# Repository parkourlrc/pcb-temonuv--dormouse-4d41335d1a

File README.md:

<div align="center">

# 🐭 Dormouse

**A tiny, coin-cell Zigbee climate sensor that hibernates like its namesake — years on a CR2032, and joins Home Assistant with zero cloud.**

[-2f6db3)](https://www.silabs.com/wireless/zigbee)

</div>

---

## What it is

**Dormouse** is a from-scratch, open-hardware **temperature + humidity sensor** on the
Silicon Labs **MGM210LA22JNF2** module (EFR32MG21, Cortex-M33, 2.4 GHz). It's a Zigbee
**sleepy end device**: it wakes every 5 minutes, reads an external **Sensirion SHT40**
over I²C, reports temperature, relative humidity and battery level over Zigbee, then
drops back to EM2 sleep. On a single **CR2032** that budgets out to **multi-year**
battery life. No hub beyond your existing Zigbee coordinator, no cloud, no vendor lock-in.

> **Why "Dormouse"?** A dormouse hibernates and briefly stirs to feed — which is
> exactly what a Zigbee sleepy end device does: sleep deep in EM2, wake for a few
> milliseconds every five minutes, report, and doze off again.

Everything is here: **firmware**, a **custom KiCad schematic + routed 2-layer PCB**,
a **datasheet-exact module footprint**, the **manufacturing files**, and the
**Home Assistant integration**.

## ✨ Highlights

- 🔋 **Coin-cell native** — sleepy end device, EM2 sleep, TX power capped so a CR2032 never browns out. ~1–3 µA average.
- 🌡️ **Real ambient temp + humidity** — external SHT40 (±0.2 °C / ±1.8 %RH), CRC-checked, one-shot read per wake.
- 🏠 **Zero-config Home Assistant** — temperature, humidity and battery auto-expose over **ZHA**; a ready-made **Zigbee2MQTT** converter is included.
- 🐞 **Runtime debug mode** — flip a switch in HA to drop to 10 s sampling and stream a live log line, over a manufacturer-specific Zigbee cluster. Auto-off on boot so it never drains the cell.
- 🛡️ **Self-healing** — software watchdog (spans the multi-minute sleep), I²C bus recovery, and a **button-less factory reset** (power-cycle 5× quickly → re-commission).
- 🛠️ **Fully open & reproducible** — headless `slc generate` → build → flash; schematic + footprint generated by scripts; DRC-clean routed board; Gerbers included.

---

## 📸 Gallery

| Top | Bottom (CR2032 holder) |
|:---:|:---:|
|  |  |

<div align="center"></div>

---

## 🧩 How it works

```
         ┌──────────────────────────── every 5 min (10 s in debug) ────────────────────────────┐
         │                                                                                      │
   wake ─┤  SHT40 read (I²C, CRC)  →  IADC battery read  →  write ZCL attrs  →  reporting  →  EM2 sleep
         │        temp + RH               VDD via AVDD/4        temp/RH/batt      pushes to
         │                                                                        coordinator
         └──────────────────────────────────────────────────────────────────────────────────────┘

  ZCL model (endpoint 1, HA Temperature Sensor 0x0302):
    Basic · Power Config · Identify · Temperature (0x0402) · Humidity (0x0405) · MGM Debug (0xFC10)
```

The `.slcp` manifest is the **source of truth** for components, the target part,
sleepy-device timing and TX power. The ZCL data model lives in a ZAP file; the
`#define`s in `src/app.h` mirror it. See [`CLAUDE.md`](CLAUDE.md) for the full
architecture write-up.

---

## 🔧 Hardware

Tiny **2-layer, ~36 × 25 mm** board. The MGM210L sits at the top edge with its
**integrated antenna** pointing off-board and a copper keepout around it; the
CR2032 holder is on the back; the SHT40 is at the bottom edge for airflow.

### Bill of materials

| Ref | Part | Purpose |
|-----|------|---------|
| U1 | **MGM210LA22JNF2** | MCU + Zigbee radio (integrated antenna) |
| U2 | **Sensirion SHT40** (SHT40-AD1B) | Temp + humidity, I²C 0x44 |
| BT1 | CR2032 SMD holder | Power (~220 mAh) |
| R1, R2 | 4.7 kΩ (0402) | I²C pull-ups |
| C1 | 10 µF (0805) | Bulk decoupling — sources the TX pulse |
| C2, C3 | 100 nF (0402) | HF decoupling (module + sensor) |
| J1 | 1×5 1.27 mm header | SWD / RTT debug |

Full wiring, pinout and CR2032 power design: **[`docs/hardware.md`](docs/hardware.md)**.
KiCad sources, custom libraries and PCB notes: **[`hardware/README.md`](hardware/README.md)**.
Manufacturing files (Gerbers, drill, BOM, pick-and-place): **[`hardware/fab/`](hardware/fab/)**.

---

## 🚀 Build & flash

There is **no host/unit-test suite** — this is on-target firmware. "Testing" means
flashing and watching the join + reports over RTT and in ZHA/Z2M. The toolchain is
installed via **SLT** (Silicon Labs Tool).

```bash
# one-time: install SDK 2026.6.0 + slc/gcc/zap/commander
slt install -f tools/pkg.slt

source tools/env.sh      # puts slc, arm-none-eabi-gcc, commander, zap on PATH
tools/build.sh           # slc generate (runs ZAP) + make  ->  build/…/*.s37
tools/flash.sh           # commander flash over J-Link
commander rtt --device MGM210LA22JNF   # live device logs
```

Then put your Zigbee network in join mode (ZHA: *Add device*; Z2M: `permit_join`)
and power the sensor. Verified working with SDK 2026.6.0, slc-cli 6.0.22, GCC 14.2.

---

## 🏠 Home Assistant

- **ZHA** — temperature, humidity and battery are **zero-config** (standard clusters).
  The custom debug cluster needs a small [ZHA quirk](https://github.com/zigpy/zha-device-handlers) to expose.
- **Zigbee2MQTT** — drop [`integration/zigbee2mqtt/dormouse.js`](integration/zigbee2mqtt/dormouse.js)
  in as an external converter. It exposes temperature, humidity, battery, and the
  debug entities (`debug_mode` switch, `debug_log`, `debug_status`, `sample_interval`).

---

## 🗂️ Repository layout

| Path | What |
|------|------|
| `mgm210l_zigbee_temp.slcp` | Project manifest — components, target, config. **Source of truth.** |
| `src/` | Firmware: measurement loop, SHT40 driver, battery, debug mode, watchdog, factory reset. |
| `config/zcl/` | ZCL data model (ZAP) + custom debug-cluster XML. |
| `hardware/` | KiCad schematic + routed PCB, custom symbol/footprint libraries, generators. |
| `hardware/fab/` | Gerbers, drill, BOM, pick-and-place — ready to send to a fab. |
| `integration/zigbee2mqtt/` | Z2M external converter. |
| `docs/` | Hardware guide + rendered images. |
| `tools/` | Headless build / flash / env scripts. |
| `CLAUDE.md` | Deep-dive architecture & rationale (great first read for contributors). |

---

## 🗺️ Roadmap

### ✅ Done
- [x] Firmware builds end-to-end (`slc generate` → compile → link → flashable `.s37`)
- [x] ZCL model: temperature, humidity, power config, + manufacturer debug cluster (`0xFC10`)
- [x] SHT40 I²C driver — CRC-8 verified, with automatic I²C bus recovery + one retry
- [x] Battery sensing via internal IADC (no divider), with a bounded busy-wait guard
- [x] Sleepy-end-device power model (EM2 sleep, 300 s poll, 8 dBm TX cap)
- [x] Runtime debug mode (HA-controlled 10 s cadence + live log), auto-off on boot
- [x] Software watchdog (sleeptimer-based, spans multi-minute sleep)
- [x] Button-less power-cycle factory reset (5× quick cycles → re-commission)
- [x] Custom, datasheet-exact MGM210LA22JNF land pattern + symbol library
- [x] 2-layer PCB fully routed, GND pours with antenna keepout, **0 copper DRC errors**
- [x] Manufacturing package generated (Gerbers / drill / BOM / pick-and-place)
- [x] **PCBs ordered** 🎉
- [x] Zigbee2MQTT converter + ZHA zero-config path
- [x] GitHub Actions CI — repo + device-identity checks on every push (`ci.yml`); firmware `.s37` build & release via a self-hosted runner (`firmware.yml`)

### 🔜 Next (hardware bring-up)
- [ ] Assemble the boards (reflow / hand-solder), first power-on
- [ ] Flash and confirm join + temperature/humidity/battery reports in ZHA & Z2M
- [ ] Verify TX power reads 8 dBm on RTT after a warm-reboot join
- [ ] Confirm `FACTORY_RESET_NVM3_KEY` has no stack-key collision; test the 5× power-cycle reset
- [ ] Double-check `config/sl_i2cspm_sensor_config.h` pins match the built board (PC00/PC01)
- [ ] Measure real sleep current & validate multi-year battery estimate

### 💡 Ideas / help wanted
- [ ] ZHA quirk (zha-device-handlers) so the debug cluster shows up as HA entities
- [ ] 3D model for the custom MGM210L footprint (nicer renders + mechanical check)
- [ ] 3D-printed enclosure / vented case for the SHT40
- [ ] Production build profile (drop `segger_rtt` / `iostream_rtt` to shave idle current)
- [ ] Si7021 sensor variant (swap command byte + conversion only)
- [ ] Zigbee OTA firmware update support
- [ ] Nudge the one SDA trace to clear the cosmetic 0.05 mm edge-clearance DRC note

---

## 🤝 Contributing

Issues and PRs welcome — especially hardware bring-up reports, battery-life data,
and the "help wanted" items above. Please read [`CLAUDE.md`](CLAUDE.md) first; it
explains the two-stage build, the `.slcp`-is-truth rule, and the ZCL/`app.h`/converter
sync requirement that's easy to trip over.

## 📄 License

MIT — see [`LICENSE`](LICENSE). Firmware builds against the Silicon Labs Simplicity
SDK, which carries its own (permissive) license; it is **not** vendored here — the
build fetches it via SLT.

## 🙏 Acknowledgements

- Silicon Labs — EFR32MG21 / MGM210L, Simplicity SDK, Zigbee stack.
- Sensirion — SHT4x sensor family.
- The **KiCad**, **Freerouting**, and **Zigbee2MQTT** projects.

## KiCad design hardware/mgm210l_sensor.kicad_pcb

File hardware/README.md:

# Hardware — schematic + PCB

KiCad 8/9 design for **Dormouse**, the MGM210L CR2032 temperature + humidity
sensor. The schematic (electrical connectivity) and the routed PCB are both here.
(File basenames stay `mgm210l_sensor.*` — renaming a finalized, already-ordered
KiCad project risks breaking internal references for no functional gain.)

| File | What |
|------|------|
| `mgm210l_sensor.kicad_pro` | KiCad project — open this in KiCad. |
| `mgm210l_sensor.kicad_sch` | Schematic (generated by `gen_sch.py`). |
| `mgm210l_sensor.kicad_pcb` | PCB — placement + antenna keepout + GND pours + full routing. |
| `mgm210l_sensor.pdf` | Rendered schematic (quick view, no KiCad needed). |
| `mgm210l_sensor_2d_view.png` | Rendered PCB (top view). |
| `mgm210l_sensor_enclosure_drawing.pdf` | Dimensioned mechanical drawing for 3D-printed enclosure design (outline, placement, Z stack-up). |
| `gen_sch.py` | Generator — schematic + `mgm.kicad_sym` are produced from this. |
| `gen_mgm_footprint.py` | Generator — the custom MGM210L land pattern. |
| `gen_enclosure_drawing.py` | Generator — the enclosure drawing PDF (parses the PCB directly). |
| `mgm.kicad_sym` | Custom symbol library (MGM210L, SHT40, SWD). |
| `mgm.pretty/` | Custom footprint library (MGM210LA22JNF land pattern). |
| `sym-lib-table` / `fp-lib-table` | Project library tables (register `Device`/`mgm`). |

> **Not committed (regenerable, `.gitignore`d):** the netlist (`.net`), text reports
> (`-drc.rpt`/`-erc.rpt`/`_drc_violations.json`), Freerouting exchange files
> (`.dsn`/`.ses`), and a local BOM copy — recreate them with the commands below.
> The canonical BOM + pick-and-place live in [`fab/`](fab/).

## Regenerate + re-export
```bash
cd hardware
python3 gen_sch.py            # -> .kicad_sch, .kicad_pro, mgm.kicad_sym
python3 gen_mgm_footprint.py  # -> mgm.pretty/MGM210LA22JNF.kicad_mod
python3 gen_enclosure_drawing.py  # -> mgm210l_sensor_enclosure_drawing.pdf (from the PCB)
kicad-cli sch export pdf     -o mgm210l_sensor.pdf mgm210l_sensor.kicad_sch
kicad-cli sch export netlist -o mgm210l_sensor.net mgm210l_sensor.kicad_sch
kicad-cli sch erc  mgm210l_sensor.kicad_sch     # 0 violations
kicad-cli pcb drc  mgm210l_sensor.kicad_pcb     # 0 errors (see PCB status below)
```
The PCB is **not** regenerated by a script — it is built from the schematic with
KiCad's "Update PCB from Schematic" (F8) and then edited. Do not expect `gen_*.py`
to touch it.

## Nets (verified from the exported netlist)
- **VDD** — CR2032(+), MGM210L pin 13, SHT40 VDD, both 4.7 kΩ pull-ups, all three
  decoupling caps, SWD header VDD.
- **GND** — CR2032(−), MGM210L pins 6 & 14, SHT40 VSS, all caps, SWD header GND.
- **SDA** — MGM210L PC01 (pin 8), SHT40 SDA (pin 1), pull-up R1.
- **SCL** — MGM210L PC00 (pin 7), SHT40 SCL (pin 2), pull-up R2.
- **SWCLK (PA01) / SWDIO (PA02) / RESETn (pin 11)** — MGM210L ↔ SWD header.
- Unused module pins (PA03/PA04, PD00/PD01, PC02–PC05, DEC pin 5, DNC pin 12) are
  flagged **no-connect**. No RF net — the antenna is integrated in the module.

Pin numbering is datasheet-accurate: MGM210L per Data Sheet Rev 1.5 Table 6.1,
SHT40 per Sensirion SHT4x §5.4 (1=SDA, 2=SCL, 3=VDD, 4=VSS). The footprint pad
numbers match the symbol pin numbers, so they connect correctly.

## Footprints
| Ref | Footprint |
|-----|-----------|
| U1 | `mgm:MGM210LA22JNF` — **custom**, from datasheet §8.2 Table 8.1 (see below) |
| U2 | `Sensor_Humidity:Sensirion_DFN-4_1.5x1.5mm_P0.8mm_SHT4x_NoCentralPad` (official) |
| BT1 | `Battery:BatteryHolder_Renata_SMTU2032-LF_1x2032` (SMD coin holder) |
| R1,R2 | `Resistor_SMD:R_0402_1005Metric` |
| C1 | `Capacitor_SMD:C_0805_2012Metric` (10 µF bulk) |
| C2,C3 | `Capacitor_SMD:C_0402_1005Metric` (100 nF) |
| J1 | `Connector_PinHeader_1.27mm:PinHeader_1x05_P1.27mm_Vertical` |

The passive/battery/header sizes are sensible defaults for a coin-cell sensor —
change them in the `FOOTPRINTS` dict in `gen_sch.py` if you prefer 0603, a
different coin holder, or a Tag-Connect debug pad.

### MGM210LA22JNF land pattern (`gen_mgm_footprint.py`)
The **pads are datasheet-exact** (positions/sizes from the MGM210L Data Sheet
Rev 1.5, §8.2 Table 8.1): three castellated edges of 6 pads each — left/bottom
1.1 × 1.6 mm at 1.71 mm pitch, right (power) 1.3 × 3.3 mm at 1.90 mm pitch. Pad
numbers match the module pinout. The **silk/courtyard are an approximation** of
the 13.0 × 15.5 mm body (documentation only), with the top edge marked as the
integrated-antenna keepout and the bottom-layer VDD test-point keepout at
(2.65, 6.45). Verify against the datasheet before ordering.

## PCB status (routed)
- **Board:** 36.0 × 25.05 mm, 2 mm corner radius, 1.6 mm FR4, 2-layer.
- **Placement:** MGM210L (U1) at the top edge with its antenna toward the board
  edge — the antenna end of the module **overhangs the top board edge by ~2.6 mm**
  (deliberate, for antenna clearance); CR2032 holder (BT1) on the **back** (B.Cu);
  SHT40 (U2) near the bottom edge for airflow; decoupling by U1's power pads;
  I²C pull-ups on the bus.
- **Ventilation:** a through slot (~7.2 × 0.7 mm) is milled in the board directly
  at the SHT40 (U2) for faster RH response.
- **Antenna keepout:** the GND pours on both layers stop 8 mm short of the top
  edge, keeping copper/ground clear of the integrated antenna (datasheet §7).
- **Ground pours:** F.Cu + B.Cu, net GND.
- **Routing:** *complete.* All six signal/power nets (SWCLK, SWDIO, RESETn, SDA,
  SCL, VDD) are routed on two layers; GND returns through the pours. Autorouted
  with Freerouting, then the three final hops into the SHT40 were hand-finished
  with vias so they approach the pads from outside the sensor keepout.
- **DRC:** **0 copper errors** — no shorts, clearance, or keepout violations, and
  0 schematic-parity errors. Remaining reports are only: 7 GND "unconnected"
  (they close the instant zones are filled — headless tools don't fill zones) and
  3 cosmetic warnings on the placed U1 (pin-1 silk dot, back-layer note, and a
  lib-mismatch) — all already fixed in `mgm.pretty`.

### To finalise in KiCad
1. Open the board and **Fill All Zones** (B) — this completes the GND net and
   clears the 7 GND ratsnest items.
2. **Update Footprints from Library** (U1) — clears the 3 cosmetic warnings by
   pulling the corrected `mgm:MGM210LA22JNF`.
3. Optional: review trace widths vs. peak TX current; re-run DRC. (The RH vent
   slot at U2 is already cut into the board — see "Ventilation" above.)

## Library note
`fp-lib-table` / `sym-lib-table` register the project-local `mgm` libraries via
`${KIPRJMOD}` (portable). For the headless KiCad-MCP backend to also resolve the
custom footprint, `mgm` was additionally added to the **global** KiCad 9
`fp-lib-table` (`~/.config/kicad/9.0/fp-lib-table`) with an absolute path — remove
that line if you relocate the project.

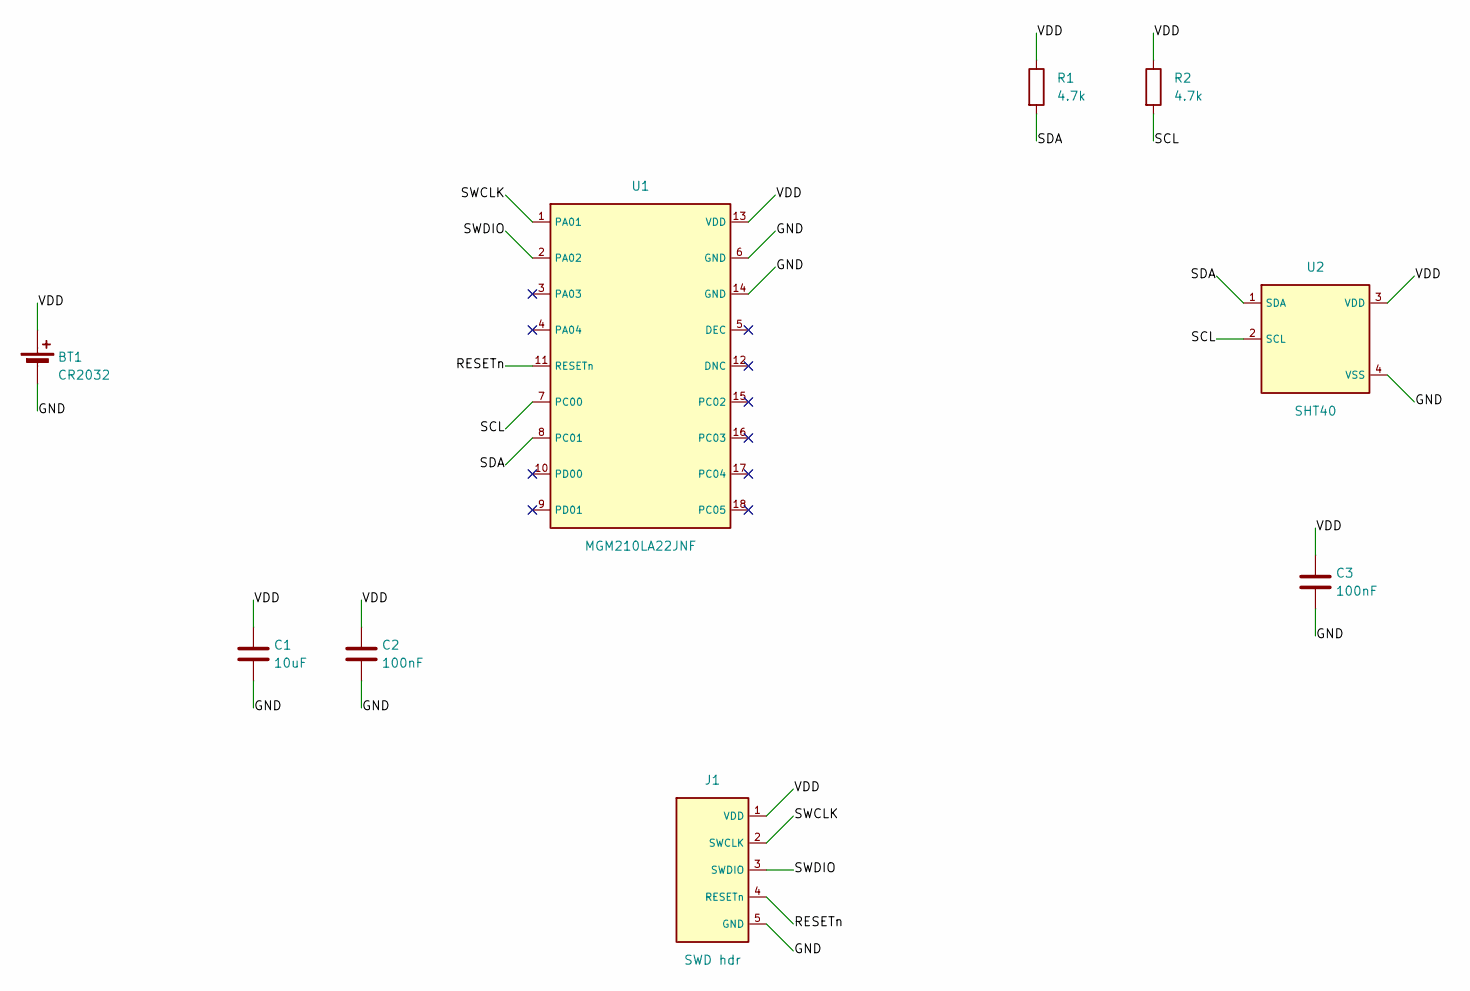
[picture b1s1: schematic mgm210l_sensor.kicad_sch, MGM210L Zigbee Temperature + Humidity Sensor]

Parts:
BT1: CR2032; BatteryHolder_Renata_SMTU2032-LF_1x2032
C1: 10uF; C_0805_2012Metric
C2, C3: 100nF; C_0402_1005Metric
J1: SWD hdr; PinHeader_1x05_P1.27mm_Vertical
R1, R2: 4.7k; R_0402_1005Metric
U1: MGM210LA22JNF
U2: SHT40; Sensirion_DFN-4_1.5x1.5mm_P0.8mm_SHT4x_NoCentralPad

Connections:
GND: BT1.2 (-), C1.2, C2.2, C3.2, J1.5 (GND), U1.6 (GND), U1.14 (GND), U2.4 (VSS)
RESETn: J1.4 (RESETn), U1.11 (RESETn)
SCL: R2.2, U1.7 (PC00), U2.2 (SCL)
SDA: R1.2, U1.8 (PC01), U2.1 (SDA)
SWCLK: J1.2 (SWCLK), U1.1 (PA01)
SWDIO: J1.3 (SWDIO), U1.2 (PA02)
VDD: BT1.1 (+), C1.1, C2.1, C3.1, J1.1 (VDD), R1.1, R2.1, U1.13 (VDD), U2.3 (VDD)

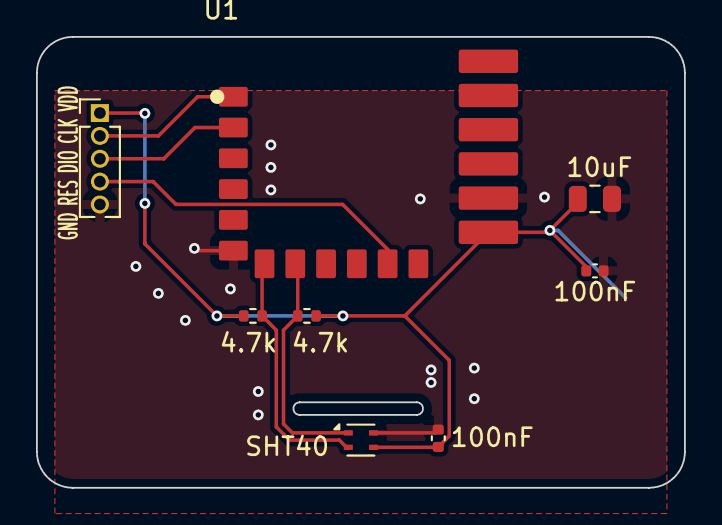
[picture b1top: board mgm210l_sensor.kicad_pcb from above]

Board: 2 copper layers, 36.0 x 25.0 mm, 9 parts (1 on the bottom side), 7 nets.

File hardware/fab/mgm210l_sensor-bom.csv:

"Refs","Value","Footprint","Qty","DNP"
"BT1","CR2032","Battery:BatteryHolder_Renata_SMTU2032-LF_1x2032","1",""
"C1","10uF","Capacitor_SMD:C_0805_2012Metric","1",""
"C2,C3","100nF","Capacitor_SMD:C_0402_1005Metric","2",""
"J1","SWD hdr","Connector_PinHeader_1.27mm:PinHeader_1x05_P1.27mm_Vertical","1",""
"R1,R2","4.7k","Resistor_SMD:R_0402_1005Metric","2",""
"U1","MGM210LA22JNF","mgm:MGM210LA22JNF","1",""
"U2","SHT40","Sensor_Humidity:Sensirion_DFN-4_1.5x1.5mm_P0.8mm_SHT4x_NoCentralPad","1",""
